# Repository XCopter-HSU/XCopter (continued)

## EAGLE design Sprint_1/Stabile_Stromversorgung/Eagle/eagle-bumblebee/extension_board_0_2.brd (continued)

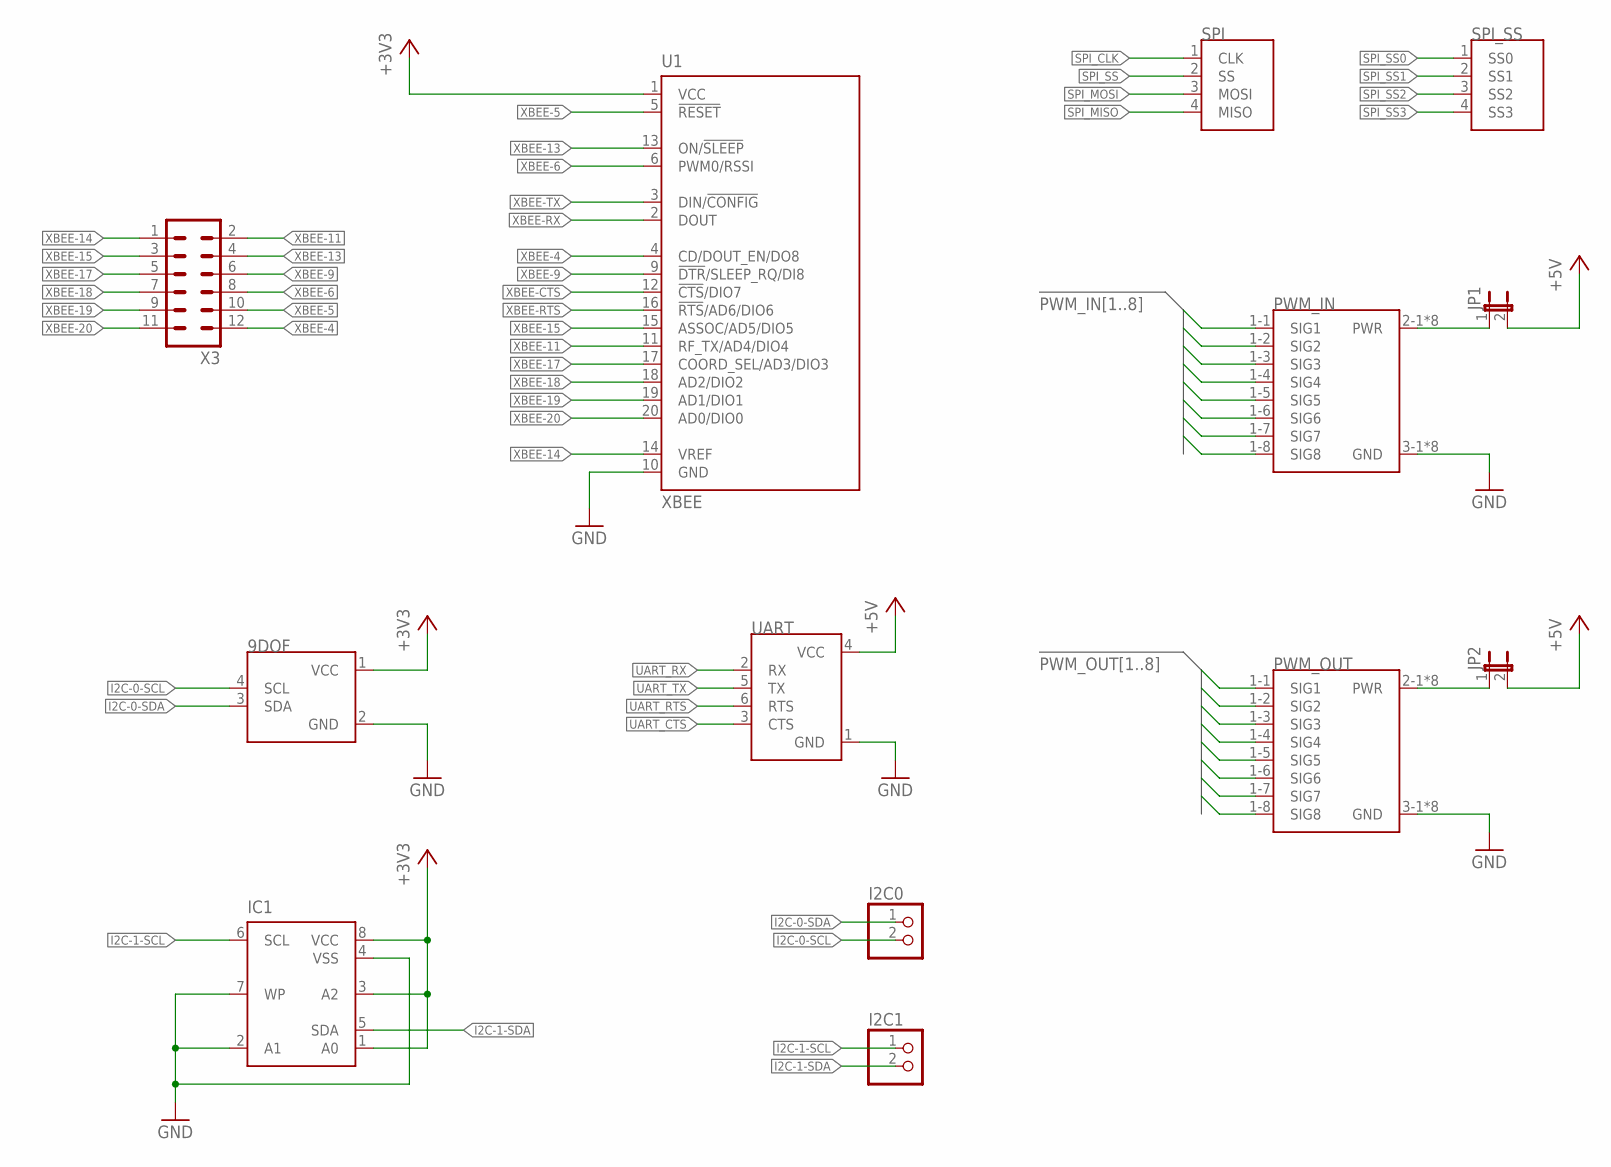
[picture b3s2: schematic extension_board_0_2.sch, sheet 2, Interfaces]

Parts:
9DOF: I2C; MA04-1
I2C0, I2C1: PINHD-1X2; 1X02
IC1: NE555; DIL-08
JP1, JP2: JP1E; JP1
PWM_IN: 8RX; MA08-3
PWM_OUT: 8RX; MA08-3
SPI: SPI_MAIN; MA04-1
SPI_SS: SPI_SS; MA04-1
U1: XBEE
UART: UART; MA03-2
X3: MA06-2

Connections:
+3V3: 9DOF.1 (VCC), IC1.1 (A0), IC1.3 (A2), IC1.8 (VCC), U1.1 (VCC); also elsewhere on the board
+5V: JP1.2, JP2.2, UART.4 (VCC); also elsewhere on the board
GND: 9DOF.2 (GND), IC1.2 (A1), IC1.4 (VSS), IC1.7 (WP), PWM_IN.3-1 (GND), PWM_IN.3-2 (GND), PWM_IN.3-3 (GND), PWM_IN.3-4 (GND), PWM_IN.3-5 (GND), PWM_IN.3-6 (GND), PWM_IN.3-7 (GND), PWM_IN.3-8 (GND), PWM_OUT.3-1 (GND), PWM_OUT.3-2 (GND), PWM_OUT.3-3 (GND), PWM_OUT.3-4 (GND), PWM_OUT.3-5 (GND), PWM_OUT.3-6 (GND), PWM_OUT.3-7 (GND), PWM_OUT.3-8 (GND), U1.10 (GND), UART.1 (GND); also elsewhere on the board
I2C-0-SCL: 9DOF.4 (SCL), I2C0.2; also elsewhere on the board
I2C-0-SDA: 9DOF.3 (SDA), I2C0.1; also elsewhere on the board
I2C-1-SCL: I2C1.1, IC1.6 (SCL); also elsewhere on the board
I2C-1-SDA: I2C1.2, IC1.5 (SDA); also elsewhere on the board
unnamed: JP1.1, PWM_IN.2-1 (PWR), PWM_IN.2-2 (PWR), PWM_IN.2-3 (PWR), PWM_IN.2-4 (PWR), PWM_IN.2-5 (PWR), PWM_IN.2-6 (PWR), PWM_IN.2-7 (PWR), PWM_IN.2-8 (PWR)
unnamed: JP2.1, PWM_OUT.2-1 (PWR), PWM_OUT.2-2 (PWR), PWM_OUT.2-3 (PWR), PWM_OUT.2-4 (PWR), PWM_OUT.2-5 (PWR), PWM_OUT.2-6 (PWR), PWM_OUT.2-7 (PWR), PWM_OUT.2-8 (PWR)
PWM_IN1: PWM_IN.1-1 (SIG1); also elsewhere on the board
PWM_IN2: PWM_IN.1-2 (SIG2); also elsewhere on the board
PWM_IN3: PWM_IN.1-3 (SIG3); also elsewhere on the board
PWM_IN4: PWM_IN.1-4 (SIG4); also elsewhere on the board
PWM_IN5: PWM_IN.1-5 (SIG5); also elsewhere on the board
PWM_IN6: PWM_IN.1-6 (SIG6); also elsewhere on the board
PWM_IN7: PWM_IN.1-7 (SIG7); also elsewhere on the board
PWM_IN8: PWM_IN.1-8 (SIG8); also elsewhere on the board
PWM_OUT1: PWM_OUT.1-1 (SIG1); also elsewhere on the board
PWM_OUT2: PWM_OUT.1-2 (SIG2); also elsewhere on the board
PWM_OUT3: PWM_OUT.1-3 (SIG3); also elsewhere on the board
PWM_OUT4: PWM_OUT.1-4 (SIG4); also elsewhere on the board
PWM_OUT5: PWM_OUT.1-5 (SIG5); also elsewhere on the board
PWM_OUT6: PWM_OUT.1-6 (SIG6); also elsewhere on the board
PWM_OUT7: PWM_OUT.1-7 (SIG7); also elsewhere on the board
PWM_OUT8: PWM_OUT.1-8 (SIG8); also elsewhere on the board
SPI_CLK: SPI.1 (CLK); also elsewhere on the board
SPI_MISO: SPI.4 (MISO); also elsewhere on the board
SPI_MOSI: SPI.3 (MOSI); also elsewhere on the board
SPI_SS: SPI.2 (SS); also elsewhere on the board
SPI_SS0: SPI_SS.1 (SS0); also elsewhere on the board
SPI_SS1: SPI_SS.2 (SS1); also elsewhere on the board
SPI_SS2: SPI_SS.3 (SS2); also elsewhere on the board
SPI_SS3: SPI_SS.4 (SS3); also elsewhere on the board
UART_CTS: UART.3 (CTS); also elsewhere on the board
UART_RTS: UART.6 (RTS); also elsewhere on the board
UART_RX: UART.2 (RX); also elsewhere on the board
UART_TX: UART.5 (TX); also elsewhere on the board
XBEE-4: U1.4 (CD/DOUT_EN/DO8), X3.12
XBEE-5: U1.5 (!RESET), X3.10
XBEE-6: U1.6 (PWM0/RSSI), X3.8
XBEE-9: U1.9 (!DTR!/SLEEP_RQ/DI8), X3.6
XBEE-11: U1.11 (RF_TX/AD4/DIO4), X3.2
XBEE-13: U1.13 (ON/!SLEEP), X3.4
XBEE-14: U1.14 (VREF), X3.1
XBEE-15: U1.15 (ASSOC/AD5/DIO5), X3.3
XBEE-17: U1.17 (COORD_SEL/AD3/DIO3), X3.5
XBEE-18: U1.18 (AD2/DIO2), X3.7
XBEE-19: U1.19 (AD1/DIO1), X3.9
XBEE-20: U1.20 (AD0/DIO0), X3.11
XBEE-CTS: U1.12 (!CTS!/DIO7); also elsewhere on the board
XBEE-RTS: U1.16 (!RTS!/AD6/DIO6); also elsewhere on the board
XBEE-RX: U1.2 (DOUT); also elsewhere on the board
XBEE-TX: U1.3 (DIN/!CONFIG); also elsewhere on the board

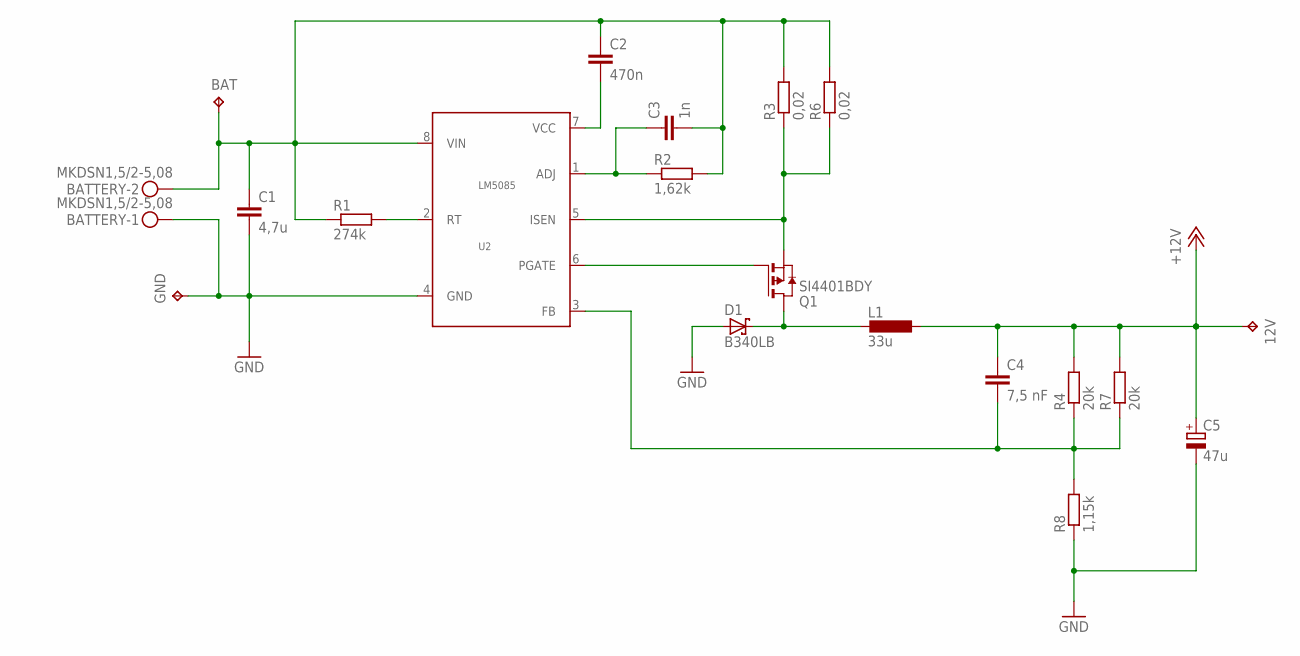
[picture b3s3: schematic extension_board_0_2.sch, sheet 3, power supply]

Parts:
12V: TPPAD1-13; P1-13
BAT: TPPAD1-13; P1-13
BATTERY: MKDSN1,5/2-5,08
C1: 4,7u; C0805
C2: 470n; C1206
C3: 1n; C1206
C4: 7,5 nF; C0603
C5: 47u; CT3216
D1: B340LB; SMB
GND: TPPAD1-13; P1-13
L1: 33u; INDUKTOR
Q1: SI4401BDY; SO8-FET
R1: 274k; R1206
R2: 1,62k; R0805
R3, R6: 0,02; R1206
R4, R7: 20k; R1206
R8: 1,15k; R0805
U2: LM5085; S-PDSO-G08

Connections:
+12V: 12V.TP, C4.1, C5.+, L1.P$2 (2), R4.2, R7.2; also elsewhere on the board
D: D1.C, L1.P$1 (1), Q1.5 (D), Q1.6 (D), Q1.7 (D), Q1.8 (D), Q1.D1 (D), Q1.D2 (D), Q1.D3 (D)
G: Q1.4 (G), U2.6 (PGATE)
GND: BATTERY.1, C1.2, C5.-, D1.A, GND.TP, R8.1, U2.4 (GND); also elsewhere on the board
unnamed: R1.2, U2.2 (RT)
unnamed: C2.2, U2.7 (VCC)
unnamed: C3.1, R2.1, U2.1 (ADJ)
unnamed: C4.2, R4.1, R7.1, R8.2, U2.3 (FB)
S: Q1.1 (S), Q1.2 (S), Q1.3 (S), R3.1, R6.1, U2.5 (ISEN)
VCC-BAT: BAT.TP, BATTERY.2, C1.1, C2.1, C3.2, R1.1, R2.2, R3.2, R6.2, U2.8 (VIN)

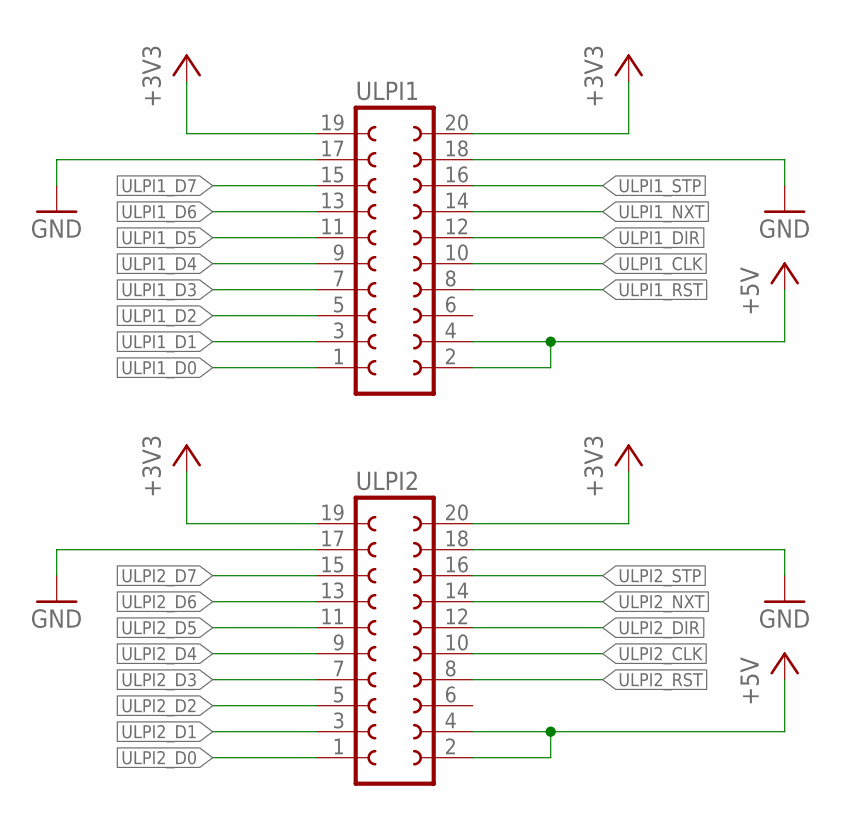
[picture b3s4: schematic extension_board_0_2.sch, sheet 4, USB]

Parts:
ULPI1, ULPI2: FE10-2W

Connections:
+3V3: ULPI1.19, ULPI1.20, ULPI2.19, ULPI2.20; also elsewhere on the board
+5V: ULPI1.2, ULPI1.4, ULPI2.2, ULPI2.4; also elsewhere on the board
GND: ULPI1.17, ULPI1.18, ULPI2.17, ULPI2.18; also elsewhere on the board
ULPI1_CLK: ULPI1.10; also elsewhere on the board
ULPI1_D0: ULPI1.1; also elsewhere on the board
ULPI1_D1: ULPI1.3; also elsewhere on the board
ULPI1_D2: ULPI1.5; also elsewhere on the board
ULPI1_D3: ULPI1.7; also elsewhere on the board
ULPI1_D4: ULPI1.9; also elsewhere on the board
ULPI1_D5: ULPI1.11; also elsewhere on the board
ULPI1_D6: ULPI1.13; also elsewhere on the board
ULPI1_D7: ULPI1.15; also elsewhere on the board
ULPI1_DIR: ULPI1.12; also elsewhere on the board
ULPI1_NXT: ULPI1.14; also elsewhere on the board
ULPI1_RST: ULPI1.8; also elsewhere on the board
ULPI1_STP: ULPI1.16; also elsewhere on the board
ULPI2_CLK: ULPI2.10; also elsewhere on the board
ULPI2_D0: ULPI2.1; also elsewhere on the board
ULPI2_D1: ULPI2.3; also elsewhere on the board
ULPI2_D2: ULPI2.5; also elsewhere on the board
ULPI2_D3: ULPI2.7; also elsewhere on the board
ULPI2_D4: ULPI2.9; also elsewhere on the board
ULPI2_D5: ULPI2.11; also elsewhere on the board
ULPI2_D6: ULPI2.13; also elsewhere on the board
ULPI2_D7: ULPI2.15; also elsewhere on the board
ULPI2_DIR: ULPI2.12; also elsewhere on the board
ULPI2_NXT: ULPI2.14; also elsewhere on the board
ULPI2_RST: ULPI2.8; also elsewhere on the board
ULPI2_STP: ULPI2.16; also elsewhere on the board

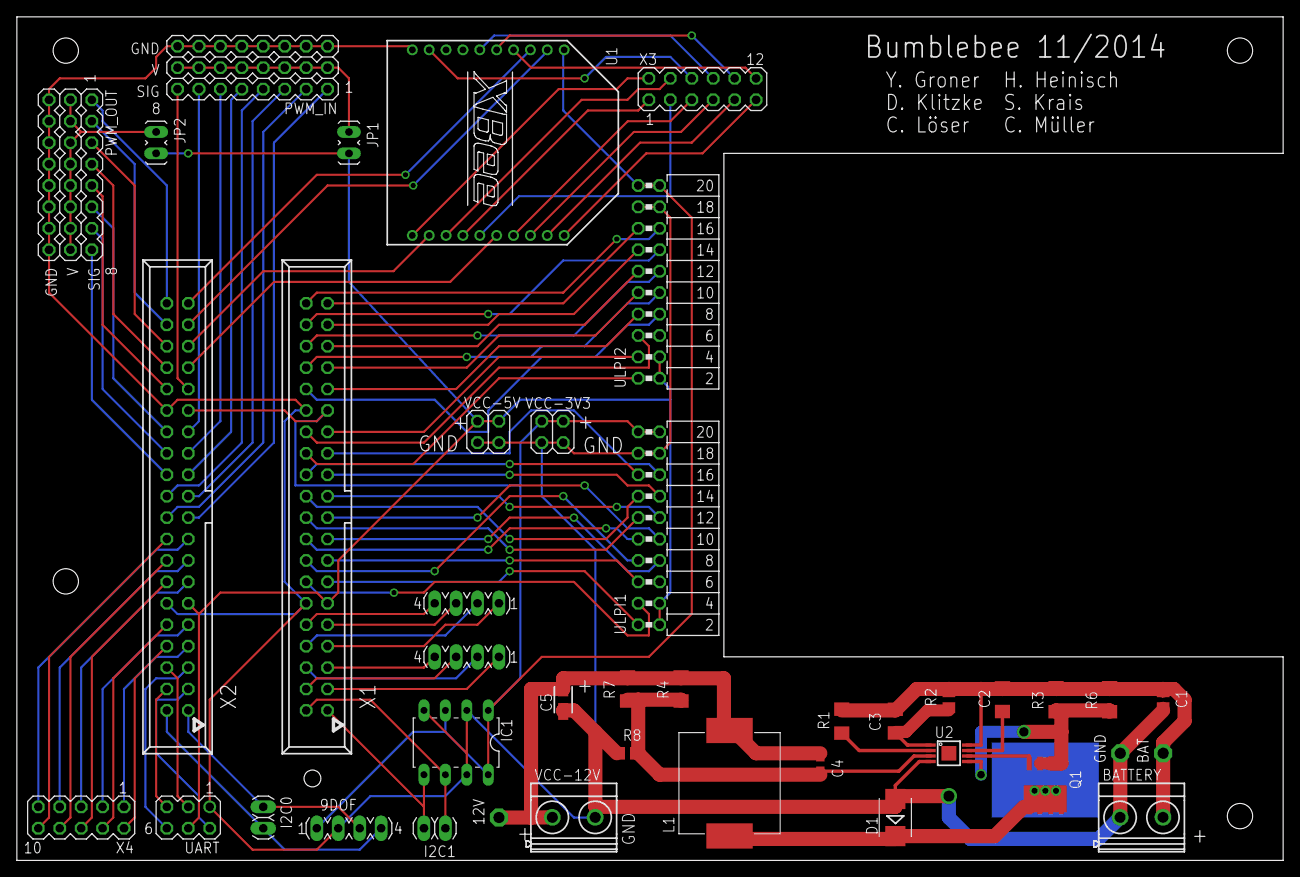
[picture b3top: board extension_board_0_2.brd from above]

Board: 2 copper layers, 150.1 x 100.0 mm, 41 parts (0 on the bottom side), 98 nets.

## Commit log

2015-03-27 Protokoll XCopter - Erstes Treffen - 26.03.15
2015-03-29 alte docs
2015-03-30 benni in der mail list geadded
2015-03-31 Create protocol31-03-2015
2015-03-31 Rename protocol31-03-2015 to 2015_03_31_TeamMeeting
2015-03-31 Rename XCopter_Treffen_01_26.03.15.txt to 2015_03_26_TeamMeeting
2015-03-31 Jira Eingetragen !
2015-04-01 renamed meeting files (added .txt)
2015-04-02 Create protokoll02-04-2015
2015-04-02 Rename protokoll02-04-2015 to 2015_04_02_SprintMeeting
2015-04-02 Rename 2015_04_02_SprintMeeting to 2015_04_02_TeamMeeting_Prof
2015-04-10 KickOff Präsentation von Herr Strahnen hochgeladen
2015-04-10 prof protokoll umbenannt in *.txt
2015-04-10 KickOff Präsentation Hochgeladen
2015-04-14 requirements of last group extracted from their documentation
2015-04-14 Impediment Backlog erstellt zum Online verwalten
2015-04-17 Test Test
    test
2015-04-17 Impediment Backlog with example we try this for this sprint 1 and maybe we change it after the sprint 1
2015-04-17 Stabile Stromversorgung files pushen
2015-04-17 Introduced Datasheet folder for all HW-Datasheets. Also added X-COP-3 documentation and notes
2015-04-17 Kleines Tutorial zum Laden der Akkus
    Siehe Titel
2015-04-17 TestFile um weitere Testdaten erweitert
2015-04-17 How-To: charging Batteries for the X-Copter Teil 1
    The first chapter of the battery charging tutorial
2015-04-17 little battery change
2015-04-17 Complete files and documents from bumblebee project
2015-04-17 Testdatei um eine Testzeile erweitert
2015-04-17 Anleitung für die Installation der Naza v2 - Flugregler Assistant software.
2015-04-17 Added a problem with the flight controller.
2015-04-17 Added the manuals and release notes for the auto pilot
2015-04-17 Datenblätter für Spannungsvorsorgung hinzugefügt
2015-04-17 Added Doku "Auswahl Fernbedienung"
2015-04-17 Starterguide für unseren ESC!
2015-04-17 Rechtschreibfehler korrigiert
2015-04-17 no message
2015-04-17 Impediment Backlog Task hinzugefügt
2015-04-17 deleted because of unsinn
2015-04-17 Titel zum bestehenden Eintrag eingefügt.
2015-04-17 added "Flugregler_Manual" (Task:XCOP23)
2015-04-17 Added manual for RC- Control
2015-04-17 Updatet Tutorial. Still not complete !
2015-04-22 recloned repo (sourcetree client bug)
2015-04-23 loginDaten.xlsx renamed
2015-04-23 schaltungs screenshots, folder structure changned
2015-04-23 Update der Hilfe für die DJI Assistant Software
2015-04-23 added software and firmware for the "mx16" rc-controller
2015-04-23 doku edited
2015-04-23 Akku Tutorial nach Word exportiert. Unvollständig.
2015-04-24 Moved the pdf out of the Datasheed-root folder
2015-04-24 Anleitung für PC verbindung hinzugefügt
2015-04-24 added Software for RC-Controller
2015-04-24 added documentation "configuration rc-controller and receiver"
2015-04-28 Version 0.8 almost ready
2015-04-30 Englische Dokumentation hinzugefügt.
2015-04-30 Kleine Zusammenfassung zur User Story "Akku laden" auf englisch. Wenn jemand mag, kann man drüberlesen und Fehler oder fehlendes anprangern.
2015-05-04 finished doc
2015-05-06 continued work on docu
2015-05-21 added requirements for usb controller
2015-05-21 Seiferts USB_Ausarbeitung
2015-05-21 translated into english
2015-05-21 Sammlung von Infos zum USB-Controller
2015-05-21 created new documents
2015-05-21 added informations
2015-05-21 created new folder "datasheet" for usb controller
2015-05-22 Neuer Ordner zur Dokumentation der Meetings und Kundengespräche
2015-05-22 rename
2015-05-22 blubb
2015-05-22 Kleine verbesserungen in der Ordnerstruktur und Protokolle
2015-05-22 Dokumentation angefangen
2015-06-11 Create Sprint2 - Planning Meeting
2015-06-11 Doc. continued
2015-06-12 Finished Sprint 1 documentation of USB-Controller. The documentation includes all the knowledge that was obtained during the first sprint in regards to the USB Controller problem.
2015-06-12 verknüpfungstest
2015-06-12 sprint 2 zeug für usb controller
2015-06-19 created file structure
2015-06-19 Docu continued
2015-06-19 added block diagram for simple flight controller
2015-06-19 minor update
2015-09-30 tutorial about how to set up a static mac-address on the de1-soc board
2015-09-30 Docs for our embedded linux from prof. Strahnen and DE1-SoC_User Manuals
2015-10-01 Hier einige Dateien von Prof. Strahen.
2015-10-01 Official make manual
2015-10-01 updated make manual
2015-10-05 Drivers for WLAN on DE1-SOC. Not working in its current state.
2015-10-05 Interim Report
2015-10-06 UML diagramm + SUMD Parser
2015-10-06 added Definition of SUMD
2015-10-06 First Version of SUMD-Implementation documentation
2015-10-06 name change
2015-10-06 Report ofthe First Flighttest
2015-10-07 Example Pictures of the SUMD Parser output.
2015-10-07 Renamed folder "Testflug" to "Flight test 1". Added an "Organization"-paragraph to the report.
2015-10-07 doku und uml model für flugcontroller
2015-10-07 Wrote the report for the 2nd flight test
2015-10-07 minor fix in ParseSUMDRawFrame.c added
2015-10-07 Added RC-Transmitter settings documentation. UART Test code added as well.
2015-10-07 PID doku
2015-10-08 Interim presentation use it for OUR slices
2015-10-08 picture
2015-10-08 added the "evaluation_by_the_team" section text for the final repot
2015-10-08 formula1 for pid doku
2015-10-08 Picture of the commercial power supply.
2015-10-08 stabile spannungsversorgung update!
2015-10-08 edited uml model from flight controller
2015-10-13 Picture for interim presentation from embedded linux
2015-10-13 linux + wlan slides
2015-10-13 powersupply slides
2015-10-13 mein teil
2015-10-13 newer version
2015-10-13 move into folder
2015-10-13 Paintskillz benutzt für kleinere korekturen
2015-10-13 wifi_report
2015-10-13 Presentation USB-Controller
2015-10-14 final report update
2015-10-14 Folien von Alex für die zwischenpräsentation über den Simple Flight Controller
2015-10-14 adding part "commercial_flightcontroler" for interim_presentation
2015-10-14 wifi
2015-10-14 changes on iterim doc
2015-10-14 forst draft of my presentation powerpoint documentation
2015-10-14 Interim präsoi
2015-10-14 adding "analysis of customer needs" part for interim_report
2015-10-14 kack zwischenbericht formatiert und zusammen geflickt TODO: querverweise, literaturverzeichnis, requirements kack
2015-10-14 docx gedöns
2015-10-28 structure of simple flight controller created, filter c method and docu
2015-11-04 Ordner Struktur aufgeräumt!
2015-11-04 weitere aufräumarbeiten in der ordnerstruktur
2015-11-04 inserted MCAPI Documentation
2015-11-04 Einpflegen des codes der Vorgängergruppe
2015-11-04 added pidToMotorMapper
2015-11-04 Code von Vorgängergruppe eingearbeitet
2015-11-04 added conf
2015-11-04 implemented PIDToMotorMapper
2015-11-04 changed motor[] to static
2015-11-04 SensorDataManager edited and SOPC-info file added
2015-11-04 matadatabullshit
2015-11-05 deleted
2016-01-05 test
2016-01-05 Added Documentation template, by Jan
2016-01-05 Gollers erste Draft
2016-01-05 Added RC related parts of documentation
2016-01-06 Thomas/Alex Sensorboard xCopter-Final Report
2016-01-07 Tutorial about the Virtual Machine, how to cross compile stuff for embedded linux and how to transfer data from ubuntu/vm to arm
2016-01-08 how to calib acc
2016-01-08 pid docu
2016-01-09 Ordner Struktur + aktuellen Final report
    .
2016-01-09 moved Vorlage
    .
2016-01-09 argh
2016-01-09 how to acc verbessert
2016-01-09 wifi report
2016-01-09 commit latest
2016-01-09 Embedded Linux Ranz
2016-01-09 Vorlage unserem Layout angepasst
2016-01-09 Layout angepasst
2016-01-09 FlightControllerBasis by Flo
2016-01-09 changes in FC basics
2016-01-09 FC basic problems added
2016-01-09 pid motor mapper
2016-01-09 Das Bild von der Tafel wo wir die Reihenfolge aufgeschrieben haben(für jan der kein whatsapp hat)
2016-01-09 first sample of presentation
2016-01-09 latest version
2016-01-09 SensorDataFilter
2016-01-09 Überarbeitete Version der Customer Needs. Bitte nochmal drüberschauen und an Goller: Literaturverweis einpflegen.
2016-01-09 PIDs & Powersupply text "fixed"..
2016-01-09 SensorDataManager, Logging, Interfaces (ranges) between Components, PWM-Signals
2016-01-09 Added new timer related part for final report. Minor changes in RC related pars as well.
2016-01-10 new System Architecture Diagram created
2016-01-10 hoffe ich mache jetzt nichts flasch und überpushe etwas...: hab das system architecture kapitel noch neu gemacht aber in der structured version...
2016-01-11 Sensordatamanager abschnitt erweitert
2016-01-11 Problems und Lessons learned. Das Gedöns hier kann sich eigentlich jeder mal durchlesen und überlegen wo noch was fehlt. Hier kann man recht gut aus dem A**** labern wenn einem was einfällt
2016-01-12 upload
2016-01-12 überarbeitete präsi
2016-01-12 Sys Arch diagram updated, Presi work started
2016-01-12 Presi work
2016-01-13 puuuuuuuuush
2016-01-13 updaaaaaaateeeed
2016-01-13 linux und scrum
2016-01-13 Added final presentation parts
2016-01-13 Changed one line
2016-01-13 Beta 0000000000000000000000000000000000000000000.1 von meiner präsi
2016-01-13 Alex's folien
2016-01-13 Beta 0.900000009 der folien von CodeCarnifex
2016-01-13 presentation beta
2016-01-13 SLIDES V.1.00000000000000000 FINAL STABLE LONG TERM SUPPORT
2016-01-13 presentation fertig!!
2016-01-13 SysArch Pic beamer rdy & updated..
2016-01-13 Slide for Logger
2016-01-14 Update final presentation
2016-01-14 Final version
2016-01-19 Added new future work parts for final report
2016-01-19 Final Bullshit
2016-01-19 Der wahrhaft letzte push von mir.
